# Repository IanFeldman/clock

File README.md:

# Precision Clock USB Hub with Thermal and Power Sensing

<div align="center">
  
</div>

## Features
- Time accurate to the second with ±5ppm drift
- Board temperature monitoring within ±0.5°C
- Dual USB power output up to a combined 1.5A
- Independent USB current/voltage measureement
- On board USB-Serial converter for easy programming/syncing
- Analog display brightness

## Build Deps
- lpc21isp (serial flasher)
- arm-none-eabi-gcc (cortex m compiler)

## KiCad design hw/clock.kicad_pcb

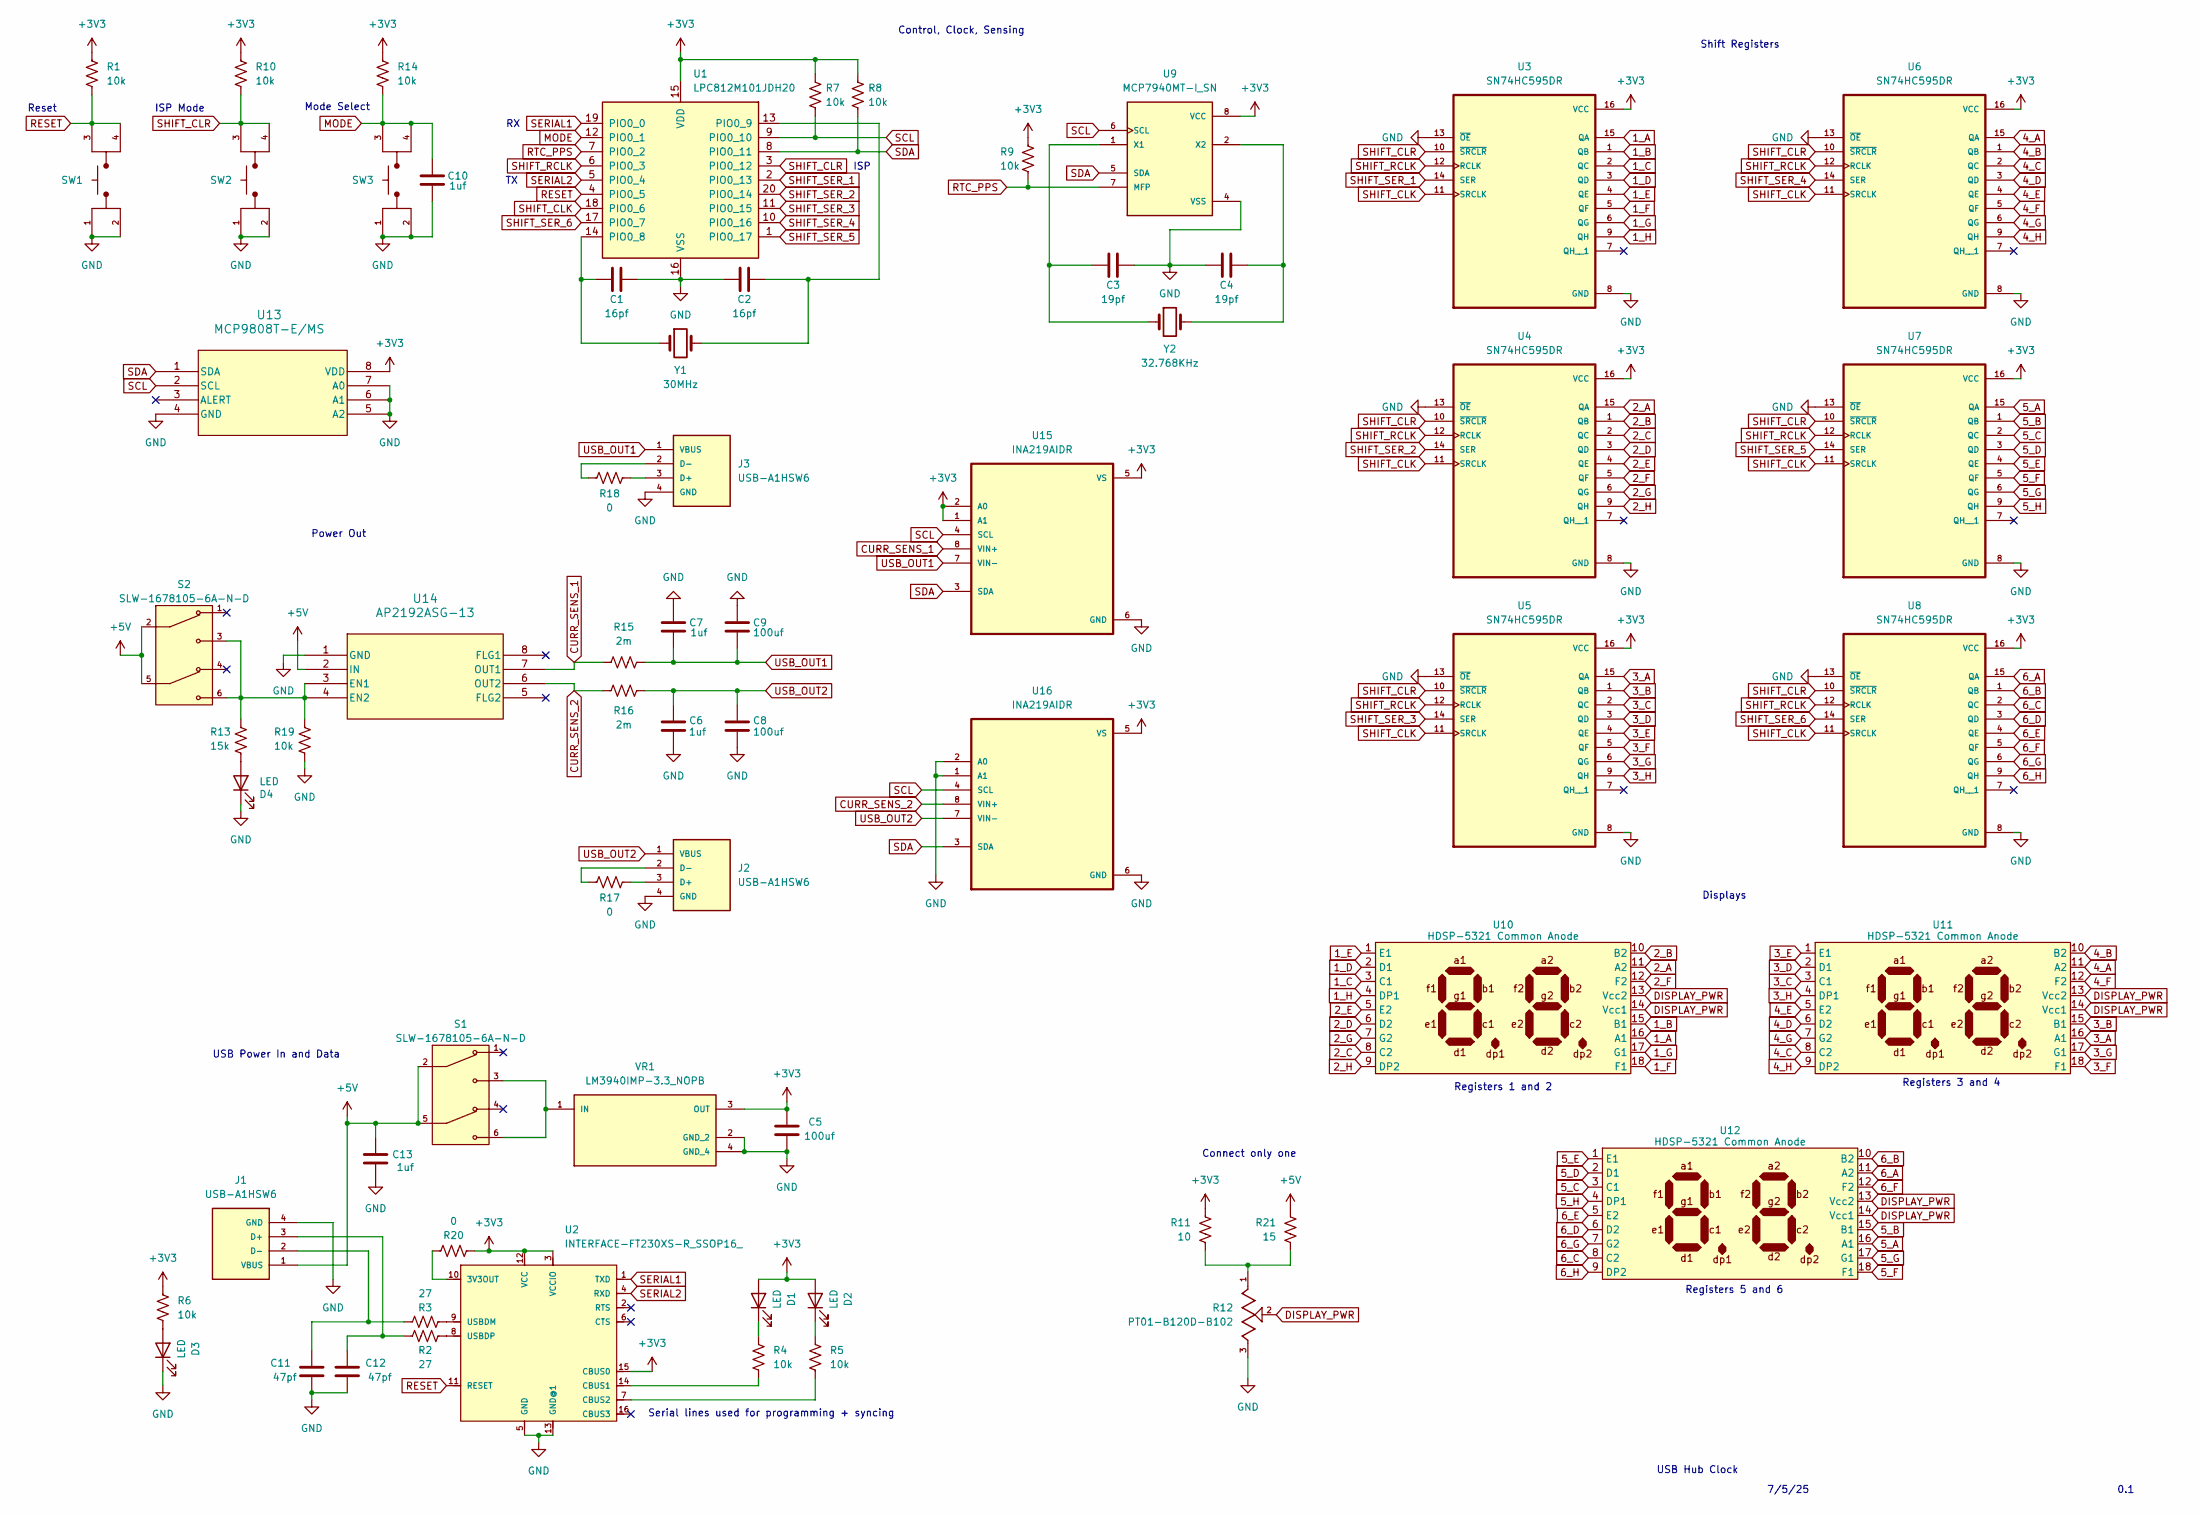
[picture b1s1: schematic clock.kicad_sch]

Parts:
C1, C2: 16pf; C_0805_2012Metric
C3, C4: 19pf; C_0805_2012Metric
C5, C8, C9: 100uf; C_0805_2012Metric
C6, C7, C10, C13: 1uf; C_0805_2012Metric
C11, C12: 47pf; C_0805_2012Metric
D1, D2, D3, D4: LED; LED_0805_2012Metric
J1, J2, J3: USB-A1HSW6; OST_USB-A1HSW6; PARTREV A
R1, R4, R5, R6, R7, R8, R9, R10, R14, R19: 10k; R_0805_2012Metric
R2, R3: 27; R_0805_2012Metric
R11: 10; R_0805_2012Metric
R12: PT01-B120D-B102; TRIM_PT01-B120D-B102; PARTREV 1.0
R13: 15k; R_0805_2012Metric
R15, R16: 2m; R_0805_2012Metric
R17, R18, R20: 0; R_0805_2012Metric
R21: 15; R_0805_2012Metric
S1, S2: SLW-1678105-6A-N-D; SW_SLW-1678105-6A-N-D; PARTREV 1.01
SW1, SW2, SW3: TL3305AF260QG; SW_TL3305AF260QG; PARTREV C
U1: LPC812M101JDH20; TSSOP-20_4.4x6.5mm_P0.65mm
U2: INTERFACE-FT230XS-R_SSOP16_; SSOP16-0.635-5X4MM; MPN FT230XS-R
U3, U4, U5, U6, U7, U8: SN74HC595DR; SOIC127P600X175-16N
U9: MCP7940MT-I_SN; SOIC127P600X175-8N
U10, U11, U12: HDSP-5321 Common Anode; HDSP-R
U13: MCP9808T-E/MS; MCP9808T
U14: AP2192ASG-13; AP2192ASG_13
U15, U16: INA219AIDR
VR1: LM3940IMP-3.3_NOPB; VREG_LM3940IMP-3.3_NOPB; PARTREV G
Y1: 30MHz; XTAL_ABLS2-30.000MHZ-D4YF-T
Y2: 32.768KHz; XTAL_ECS-.327-12.5-34RR-TR

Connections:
1_A: U3.15 (QA), U10.16 (A1)
1_B: U3.1 (QB), U10.15 (B1)
1_C: U3.2 (QC), U10.3 (C1)
1_D: U3.3 (QD), U10.2 (D1)
1_E: U3.4 (QE), U10.1 (E1)
1_F: U3.5 (QF), U10.18 (F1)
1_G: U3.6 (QG), U10.17 (G1)
1_H: U3.9 (QH), U10.4 (DP1)
2_A: U4.15 (QA), U10.11 (A2)
2_B: U4.1 (QB), U10.10 (B2)
2_C: U4.2 (QC), U10.8 (C2)
2_D: U4.3 (QD), U10.6 (D2)
2_E: U4.4 (QE), U10.5 (E2)
2_F: U4.5 (QF), U10.12 (F2)
2_G: U4.6 (QG), U10.7 (G2)
2_H: U4.9 (QH), U10.9 (DP2)
3_A: U5.15 (QA), U11.16 (A1)
3_B: U5.1 (QB), U11.15 (B1)
3_C: U5.2 (QC), U11.3 (C1)
3_D: U5.3 (QD), U11.2 (D1)
3_E: U5.4 (QE), U11.1 (E1)
3_F: U5.5 (QF), U11.18 (F1)
3_G: U5.6 (QG), U11.17 (G1)
3_H: U5.9 (QH), U11.4 (DP1)
4_A: U6.15 (QA), U11.11 (A2)
4_B: U6.1 (QB), U11.10 (B2)
4_C: U6.2 (QC), U11.8 (C2)
4_D: U6.3 (QD), U11.6 (D2)
4_E: U6.4 (QE), U11.5 (E2)
4_F: U6.5 (QF), U11.12 (F2)
4_G: U6.6 (QG), U11.7 (G2)
4_H: U6.9 (QH), U11.9 (DP2)
5_A: U7.15 (QA), U12.16 (A1)
5_B: U7.1 (QB), U12.15 (B1)
5_C: U7.2 (QC), U12.3 (C1)
5_D: U7.3 (QD), U12.2 (D1)
5_E: U7.4 (QE), U12.1 (E1)
5_F: U7.5 (QF), U12.18 (F1)
5_G: U7.6 (QG), U12.17 (G1)
5_H: U7.9 (QH), U12.4 (DP1)
6_A: U8.15 (QA), U12.11 (A2)
6_B: U8.1 (QB), U12.10 (B2)
6_C: U8.2 (QC), U12.8 (C2)
6_D: U8.3 (QD), U12.6 (D2)
6_E: U8.4 (QE), U12.5 (E2)
6_F: U8.5 (QF), U12.12 (F2)
6_G: U8.6 (QG), U12.7 (G2)
6_H: U8.9 (QH), U12.9 (DP2)
+3V3: C5.2, D1.2 (A), D2.2 (A), R1.2, R6.2, R7.2, R8.2, R9.2, R10.2, R11.2, R14.2, R20.2, U1.15 (VDD), U2.3 (VCCIO), U2.12 (VCC), U2.15 (CBUS0), U3.16 (VCC), U4.16 (VCC), U5.16 (VCC), U6.16 (VCC), U7.16 (VCC), U8.16 (VCC), U9.8 (VCC), U13.8 (VDD), U15.1 (A1), U15.2 (A0), U15.5 (VS), U16.5 (VS), VR1.3 (OUT)
+5V: C13.2, J1.1 (VBUS), R21.2, S1.2, S1.5, S2.2, S2.5, U14.2 (IN)
CURR_SENS_1: R15.2, U14.7 (OUT1), U15.8 (VIN+)
CURR_SENS_2: R16.2, U14.6 (OUT2), U16.8 (VIN+)
DISPLAY_PWR: R12.2, U10.13 (Vcc2), U10.14 (Vcc1), U11.13 (Vcc2), U11.14 (Vcc1), U12.13 (Vcc2), U12.14 (Vcc1)
GND: C1.2, C2.1, C3.2, C4.1, C5.1, C6.1, C7.1, C8.1, C9.1, C10.2, C11.1, C12.1, C13.1, D3.1 (K), D4.1 (K), J1.4 (GND), J2.4 (GND), J3.4 (GND), R12.3, R19.1, SW1.1, SW1.2, SW2.1, SW2.2, SW3.1, SW3.2, U1.16 (VSS), U2.5 (GND), U2.13 (GND@1), U3.8 (GND), U3.13 (~OE), U4.8 (GND), U4.13 (~OE), U5.8 (GND), U5.13 (~OE), U6.8 (GND), U6.13 (~OE), U7.8 (GND), U7.13 (~OE), U8.8 (GND), U8.13 (~OE), U9.4 (VSS), U13.4 (GND), U13.5 (A2), U13.6 (A1), U13.7 (A0), U14.1 (GND), U15.6 (GND), U16.1 (A1), U16.2 (A0), U16.6 (GND), VR1.2 (GND_2), VR1.4 (GND_4)
MODE: C10.1, R14.1, SW3.3, SW3.4, U1.12 (PIO0_1)
unnamed: D1.1 (K), R4.2
unnamed: D2.1 (K), R5.2
unnamed: D3.2 (A), R6.1
unnamed: D4.2 (A), R13.1
unnamed: C12.2, J1.3 (D+), R2.1
unnamed: C11.2, J1.2 (D-), R3.2
unnamed: J2.3 (D+), R17.1
unnamed: J2.2 (D-), R17.2
unnamed: J3.3 (D+), R18.1
unnamed: J3.2 (D-), R18.2
unnamed: R11.1, R12.1, R21.1
unnamed: C1.1, U1.14 (PIO0_8), Y1.1
unnamed: C2.2, U1.13 (PIO0_9), Y1.2
unnamed: R20.1, U2.10 (3V3OUT)
unnamed: R4.1, U2.14 (CBUS1)
unnamed: R5.1, U2.7 (CBUS2)
unnamed: R3.1, U2.9 (USBDM)
unnamed: R2.2, U2.8 (USBDP)
unnamed: C3.1, U9.1 (X1), Y2.1
unnamed: C4.2, U9.2 (X2), Y2.2
unnamed: R13.2, R19.2, S2.3, S2.6, U14.3 (EN1), U14.4 (EN2)
unnamed: S1.3, S1.6, VR1.1 (IN)
RESET: R1.1, SW1.3, SW1.4, U1.4 (PIO0_5), U2.11 (RESET)
RTC_PPS: R9.1, U1.7 (PIO0_2), U9.7 (MFP)
SCL: R7.1, U1.9 (PIO0_10), U9.6 (SCL), U13.2 (SCL), U15.4 (SCL), U16.4 (SCL)
SDA: R8.1, U1.8 (PIO0_11), U9.5 (SDA), U13.1 (SDA), U15.3 (SDA), U16.3 (SDA)
SERIAL1: U1.19 (PIO0_0), U2.1 (TXD)
SERIAL2: U1.5 (PIO0_4), U2.4 (RXD)
SHIFT_CLK: U1.18 (PIO0_6), U3.11 (SRCLK), U4.11 (SRCLK), U5.11 (SRCLK), U6.11 (SRCLK), U7.11 (SRCLK), U8.11 (SRCLK)
SHIFT_CLR: R10.1, SW2.3, SW2.4, U1.3 (PIO0_12), U3.10 (~SRCLR), U4.10 (~SRCLR), U5.10 (~SRCLR), U6.10 (~SRCLR), U7.10 (~SRCLR), U8.10 (~SRCLR)
SHIFT_RCLK: U1.6 (PIO0_3), U3.12 (RCLK), U4.12 (RCLK), U5.12 (RCLK), U6.12 (RCLK), U7.12 (RCLK), U8.12 (RCLK)
SHIFT_SER_1: U1.2 (PIO0_13), U3.14 (SER)
SHIFT_SER_2: U1.20 (PIO0_14), U4.14 (SER)
SHIFT_SER_3: U1.11 (PIO0_15), U5.14 (SER)
SHIFT_SER_4: U1.10 (PIO0_16), U6.14 (SER)
SHIFT_SER_5: U1.1 (PIO0_17), U7.14 (SER)
SHIFT_SER_6: U1.17 (PIO0_7), U8.14 (SER)
USB_OUT1: C7.2, C9.2, J3.1 (VBUS), R15.1, U15.7 (VIN-)
USB_OUT2: C6.2, C8.2, J2.1 (VBUS), R16.1, U16.7 (VIN-)

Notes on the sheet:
Power Out
Registers 1 and 2
7/5/25
ISP Mode
Mode Select
USB Power In and Data
Reset
USB Hub Clock
Connect only one
Registers 3 and 4
Displays
ISP
Serial lines used for programming + syncing
0.1
Control, Clock, Sensing
Shift Registers
Registers 5 and 6

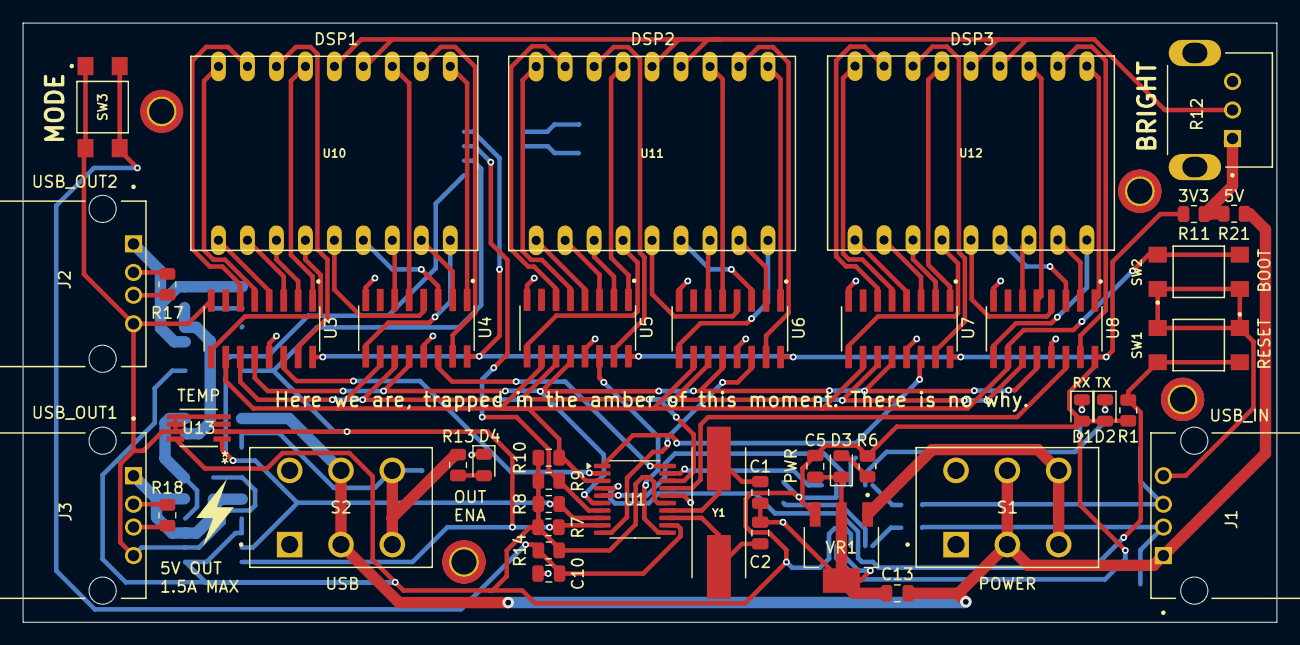
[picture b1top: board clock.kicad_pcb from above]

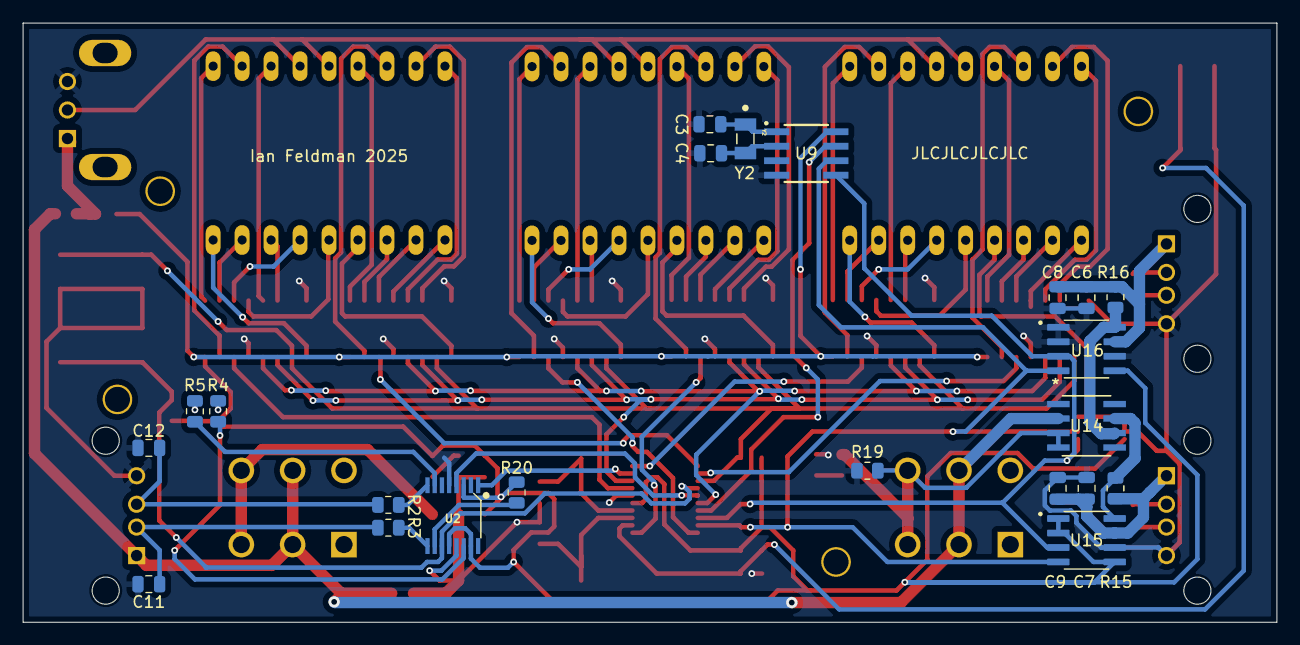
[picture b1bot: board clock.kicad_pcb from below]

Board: 2 copper layers, 109.9 x 52.5 mm, 65 parts (22 on the bottom side), 94 nets.

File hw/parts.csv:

Identifier,Value,Digikey Part Number
U1,,568-10437-5-ND
U2,,768-1135-1-ND
VR1,,LM3940IMP-3.3/NOPBCT-ND
"S1, S2",,2223-SLW-1678105-6A-N-D-ND
Y1,,535-9887-1-ND
Y2,,50-ECX-.327-CDX-1293CT-ND
"U3, U4, U5, U6, U7, U8",,296-14857-1-ND
U9,,MCP7940MT-I/SNCT-ND
R12,,2223-PT01-B120D-B102-ND
U13,,MCP9808T-E/MSCT-ND
"U15, U16",,296-23978-1-ND
U14,,AP2192ASG-13DICT-ND
"J1, J2, J3",,ED2989-ND
"SW1, SW2, SW3",,EG5353CT-ND
"C1, C2",16p,311-4228-1-ND
"C10, C6, C7, C13",1u,1276-1029-1-ND
"C11, C12",47p,311-1107-1-ND
"C3, C4",18p,311-1102-1-ND
"C5, C8, C9",100u,490-GRM21BR60G107ME11KCT-ND
"D1, D2, D3, D4",,475-LSR976-NR-1CT-ND
"R1, R10, R14, R19, R4, R5, R6, R7, R8, R9",10k,RR12P10.0KDCT-ND
R11,10,311-10.0CRCT-ND
R13,15k,A126341CT-ND
"R15, R16",2m,RHM.002AJCT-ND
"R17, R18, R20",0,P0.0ACT-ND
"R2, R3",27,311-27.0CRCT-ND
R21,15,RMCF0805FT15R0CT-ND

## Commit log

2025-06-09 Create hardware files
2025-06-09 Add USB
2025-06-12 Add voltage reg and serial converter
2025-06-12 Change mcu
2025-06-17 Shift registers
2025-06-19 Displays
2025-06-20 Variable brightness, temperature sense
2025-06-21 USB output
2025-06-24 Assign footprints
2025-06-30 Minor schematic changes, routing
2025-07-03 Place components
2025-07-03 Route top
2025-07-04 Routed
2025-07-05 Routing and minor schematic changes
2025-07-06 Update hw
2025-07-06 Final touches
2025-07-06 Move temp sensor, add quote
2025-07-06 Add pull load switch pull down
2025-07-06 Add safety resistors and 5v display backup supply
2025-07-06 Flip designator
2025-07-06 Increase usb out trace widths
2025-07-14 Change passives
2025-07-20 Add parts list
2025-07-26 Add firmware
2025-07-26 Attempt to fix boilerplate
2025-07-26 Set proper segment sizes
2025-08-03 Add display update
2025-08-05 Add i2c
2025-09-02 Add i2c write
2025-09-02 Add i2c read
2025-09-03 Start uart support
2025-11-16 Update linker and makefile to run on linux
2025-11-16 Update makefile
2025-11-16 Serial!
2025-11-16 Update i2c
2025-11-16 Read from rtc
2025-11-18 Interrupts working
2025-11-18 Software time counter
2025-11-18 Speed up display refresh
2025-11-18 Must set time on startup
2025-11-20 Programmable time
2025-11-21 Support mode button
2025-11-21 Debounce
2025-11-21 Modes
2025-11-22 Temperature
2025-11-22 Organize
2025-11-22 Fahrenheit
2025-11-24 Hours fix
